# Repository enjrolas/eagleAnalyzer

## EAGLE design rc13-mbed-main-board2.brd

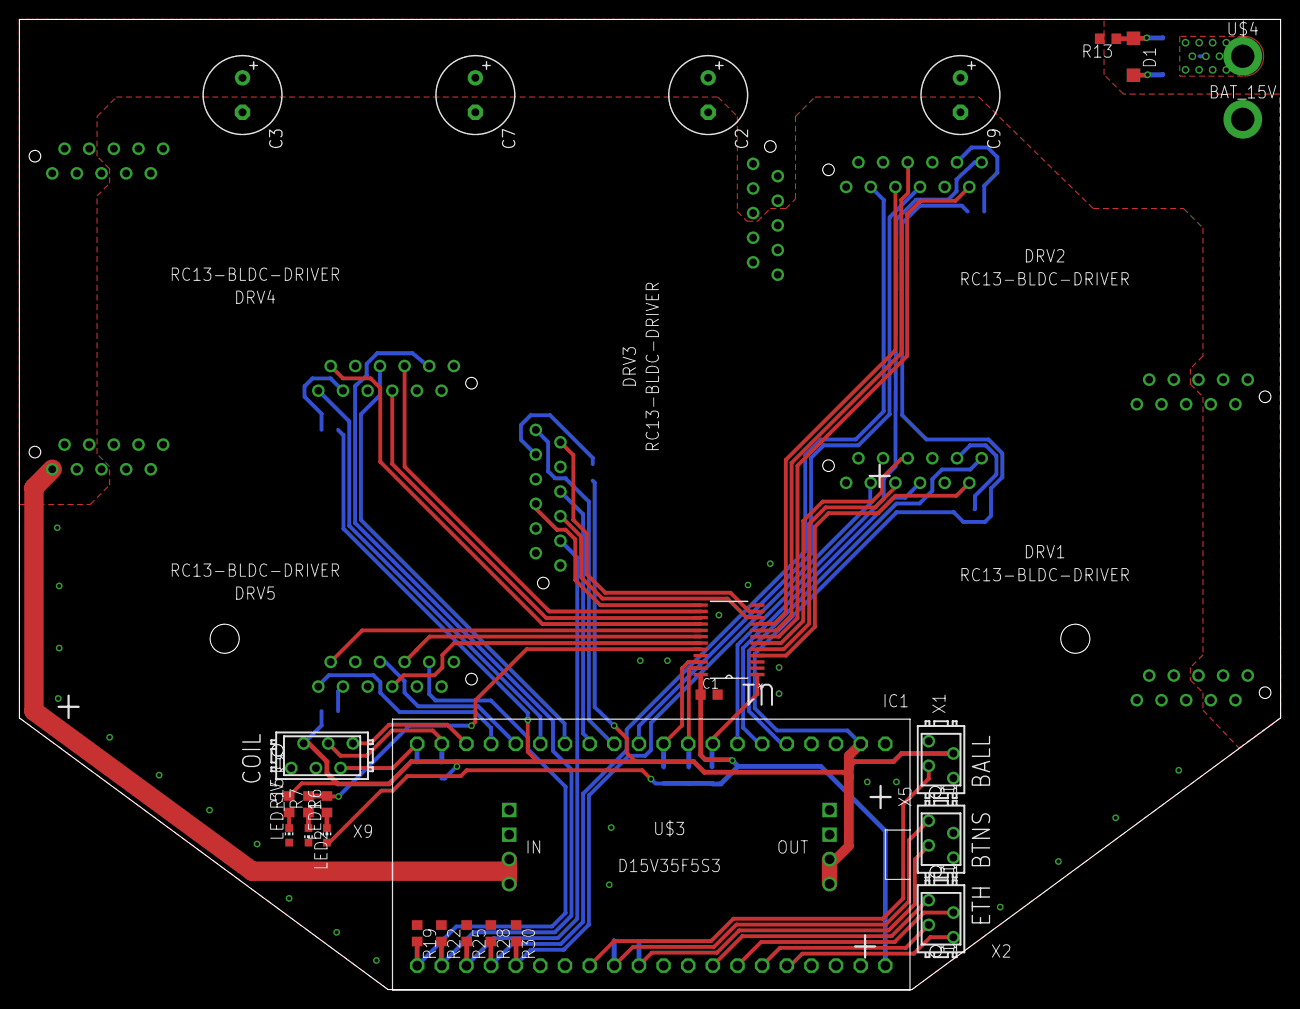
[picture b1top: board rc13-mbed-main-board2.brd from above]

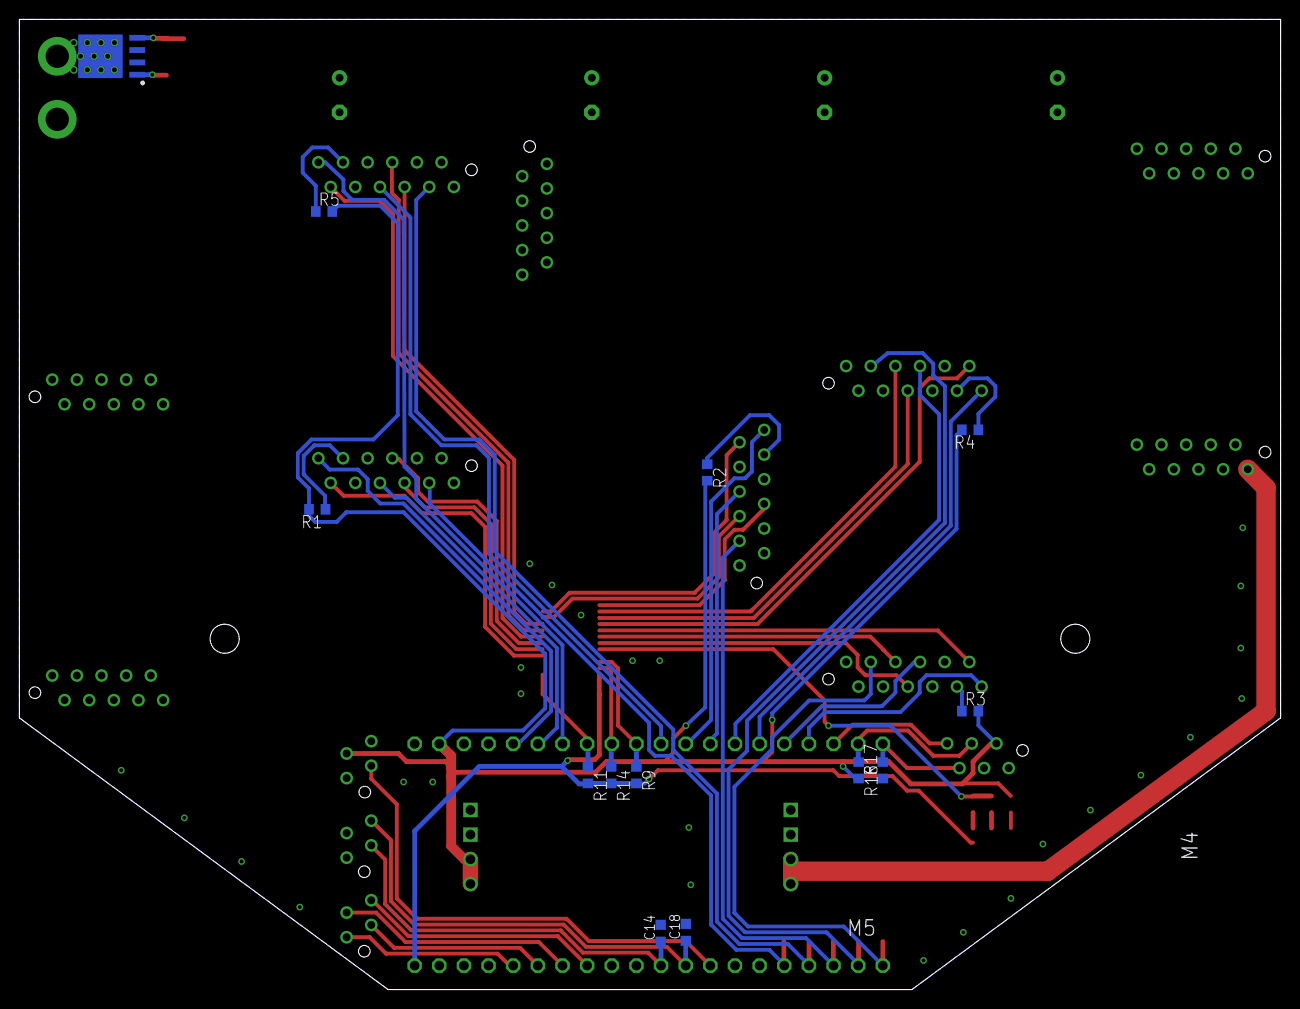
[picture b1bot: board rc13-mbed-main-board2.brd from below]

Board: 2 copper layers, 130.0 x 100.0 mm, 45 parts (13 on the bottom side), 58 nets.

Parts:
BAT_15V: M01_PWR; PWR_HOLE
C1, C14, C18: 100nF; C0603K
C2, C3, C7, C9: 470uF; E3,5-8
D1: 12V; SOD123
DRV1, DRV2, DRV3, DRV4, DRV5: RC13-BLDC-DRIVER
IC1: MBED_MICROCONTROLLER; DIL40_0.9
LED1, LED2: CHIP-LED0603
LED_5V: CHIP-LED0603
R1, R2, R3, R4, R5, R16, R17, R19, R22, R25, R28, R30: 10k; R0603
R6, R7, R9, R11, R14, R15: 2K2; R0603
R13: 100k; R0603
U1: PCA9555PW,118; SOP65P640X110-24N
U$2: MOSFET-N; TO127P600X120-5N
U$3: D15V35F5S3
U$4: M01_PWR; PWR_HOLE
X1: BALL_SENS; MICROMATCH-4
X2: ETH; MICROMATCH-4
X5: BTNS; MICROMATCH-4
X9: COIL; MICROMATCH-6

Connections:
+3V3: C1.1, IC1.40, LED1.A, R9.2, R11.2, R14.2, U1.24
+5V: IC1.2, R1.2, R2.2, R3.2, R4.2, R5.2, R15.2, R16.2, U$3.P$7, U$3.P$8, X1.3, X9.2
+15V: BAT_15V.P$1, C2.+, C3.+, C7.+, C9.+, DRV1.PWR1, DRV1.PWR2, DRV1.PWR3, DRV1.PWR4, DRV1.PWR5, DRV2.PWR1, DRV2.PWR2, DRV2.PWR3, DRV2.PWR4, DRV2.PWR5, DRV3.PWR1, DRV3.PWR2, DRV3.PWR3, DRV3.PWR4, DRV3.PWR5, DRV4.PWR1, DRV4.PWR2, DRV4.PWR3, DRV4.PWR4, DRV4.PWR5, DRV5.PWR1, DRV5.PWR2, DRV5.PWR3, DRV5.PWR4, DRV5.PWR5, R13.2, U$3.EN, U$3.P$5
BALL: IC1.28, X1.2
BAT_GND: U$2.5, U$4.P$1
BRAKE1: DRV1.LOGIC6, U1.6
BRAKE2: DRV2.LOGIC6, U1.8
BRAKE3: DRV3.LOGIC6, U1.13
BRAKE4: DRV4.LOGIC6, U1.15
BRAKE5: DRV5.LOGIC6, U1.19
BTN1: C14.1, IC1.30, X5.2
BTN2: C18.1, IC1.29, X5.4
CHARGE: IC1.20, R17.2, X9.5
COAST1: DRV1.LOGIC11, U1.4
COAST2: DRV2.LOGIC11, U1.7
COAST3: DRV3.LOGIC11, U1.11
COAST4: DRV4.LOGIC11, U1.16
COAST5: DRV5.LOGIC11, U1.17
DIR1: DRV1.LOGIC5, U1.5
DIR2: DRV2.LOGIC5, U1.9
DIR3: DRV3.LOGIC5, U1.10
DIR4: DRV4.LOGIC5, U1.14
DIR5: DRV5.LOGIC5, U1.18
DIRO1: DRV1.LOGIC12, IC1.5
DIRO2: DRV2.LOGIC12, IC1.7
DIRO3: DRV3.LOGIC12, IC1.12
DIRO4: DRV4.LOGIC12, IC1.15
DIRO5: DRV5.LOGIC12, IC1.17
DONE: IC1.18, X9.6
GND: C1.2, C2.-, C3.-, C7.-, C9.-, C14.2, C18.2, D1.A, DRV1.LOGIC1, DRV1.LOGIC2, DRV1.PWR6, DRV1.PWR7, DRV1.PWR8, DRV1.PWR9, DRV1.PWR10, DRV2.LOGIC1, DRV2.LOGIC2, DRV2.PWR6, DRV2.PWR7, DRV2.PWR8, DRV2.PWR9, DRV2.PWR10, DRV3.LOGIC1, DRV3.LOGIC2, DRV3.PWR6, DRV3.PWR7, DRV3.PWR8, DRV3.PWR9, DRV3.PWR10, DRV4.LOGIC1, DRV4.LOGIC2, DRV4.PWR6, DRV4.PWR7, DRV4.PWR8, DRV4.PWR9, DRV4.PWR10, DRV5.LOGIC1, DRV5.LOGIC2, DRV5.PWR6, DRV5.PWR7, DRV5.PWR8, DRV5.PWR9, DRV5.PWR10, IC1.1, LED2.C, LED_5V.A, R17.1, R19.1, R22.1, R25.1, R28.1, R30.1, U1.2, U1.3, U1.12, U1.21, U$2.1, U$2.2, U$2.3, U$3.P$1, U$3.P$2, U$3.P$3, U$3.P$4, X1.1, X5.1, X5.3, X9.1
INT: IC1.8, R11.1, U1.1
KICK: IC1.19, R16.1, X9.4
LED1: R6.2, R7.2, U1.20
unnamed: DRV1.LOGIC10, R1.1
unnamed: DRV2.LOGIC10, R5.1
unnamed: DRV4.LOGIC10, R4.1
unnamed: DRV5.LOGIC10, R3.1
unnamed: DRV3.LOGIC10, R2.1
unnamed: LED1.C, R6.1
unnamed: LED2.A, R7.1
unnamed: LED_5V.C, R15.1
unnamed: D1.C, R13.1, U$2.4
PWM1: DRV1.LOGIC3, IC1.25, R30.2
PWM2: DRV2.LOGIC3, IC1.24, R28.2
PWM3: DRV3.LOGIC3, IC1.23, R25.2
PWM4: DRV4.LOGIC3, IC1.22, R22.2
PWM5: DRV5.LOGIC3, IC1.21, R19.2
RD+: IC1.35, X2.2
RD-: IC1.36, X2.1
SCL: IC1.10, R9.1, U1.22
SDA: IC1.9, R14.1, U1.23
TACHO1: DRV1.LOGIC7, IC1.6
TACHO2: DRV2.LOGIC7, IC1.11
TACHO3: DRV3.LOGIC7, IC1.13
TACHO4: DRV4.LOGIC7, IC1.14
TACHO5: DRV5.LOGIC7, IC1.16
TD+: IC1.33, X2.4
TD-: IC1.34, X2.3

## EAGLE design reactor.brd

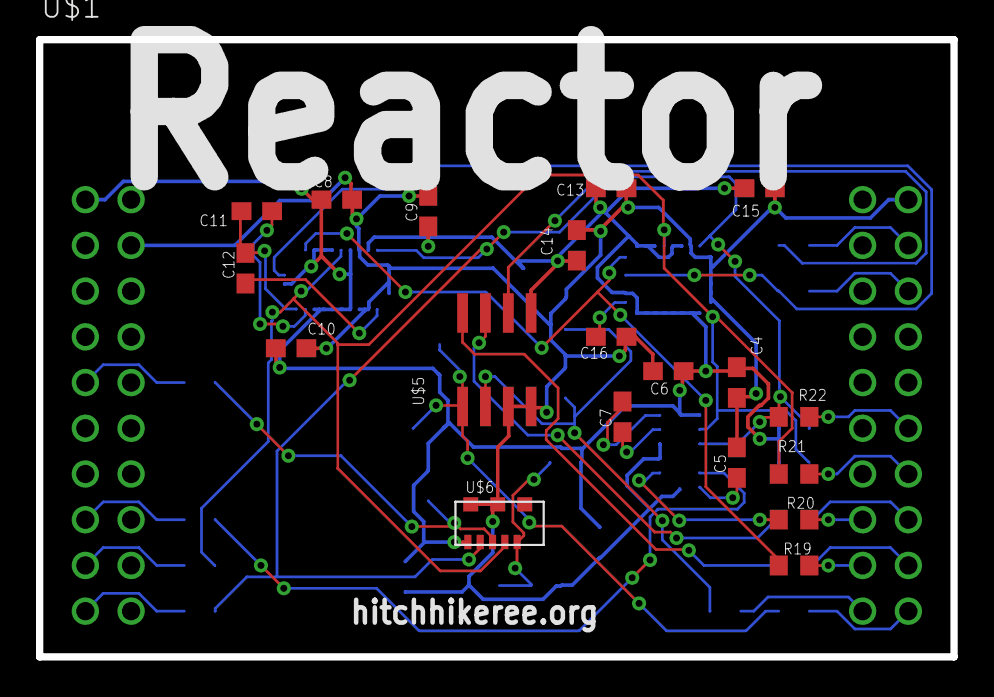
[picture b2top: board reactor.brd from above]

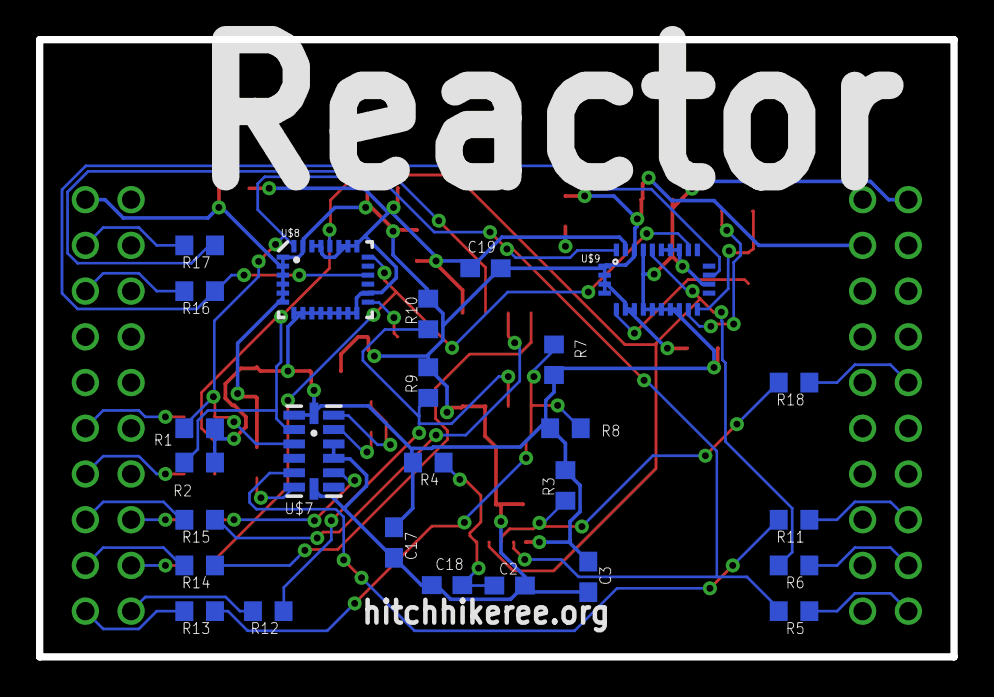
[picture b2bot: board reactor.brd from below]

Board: 2 copper layers, 50.8 x 34.3 mm, 46 parts (26 on the bottom side), 36 nets.

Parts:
C2, C3, C6, C9, C10, C14, C15, C17, C19: 0.1u; C0603
C4, C8, C13, C18: 10u; C0603
C5, C12: 4.7u; C0603
C7, C11: 0.22u; C0603
C16: 10n; C0603
R1, R2: 5.6K, 5%; R0603
R3, R7, R8: 10K; R0603
R4, R5, R6, R11, R12, R13, R14, R15, R16, R17, R18, R19, R20, R21, R22: 33; R0603
R9, R10: 10K, DNI; R0603
U$1: LAUNCHPAD_BOOSTER_PACK
U$5: SOIC8
U$6: VCNL3020
U$7: LGA14
U$8: LGA28-4X5
U$9: LGA28

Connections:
+3V3: C3.1, C4.1, C6.1, C8.1, C9.1, C10.1, C13.1, C14.1, C15.1, C17.1, C19.1, R1.2, R2.1, R3.2, R4.2, R7.1, R8.1, U$1.VCC, U$5.5, U$6.ANODE_E, U$7.1, U$7.14, U$8.7, U$8.8, U$8.9, U$8.10, U$8.11, U$8.12, U$8.13, U$8.14, U$8.16, U$8.21, U$8.22, U$8.23, U$8.25, U$8.26, U$9.8, U$9.9, U$9.10, U$9.11, U$9.12, U$9.16, U$9.21, U$9.22, U$9.23, U$9.25, U$9.27
DRDY: R20.1, U$7.9
GND: C2.2, C3.2, C4.2, C5.2, C6.2, C8.2, C9.2, C10.2, C13.2, C14.2, C15.2, C16.2, C17.2, C18.2, C19.2, R9.2, R10.2, U$1.GND@1, U$1.GND@2, U$5.3, U$5.4, U$6.CATHODE_E, U$6.VSS, U$7.7, U$7.10, U$7.11, U$8.1, U$8.2, U$8.3, U$8.4, U$8.5, U$8.6, U$8.27, U$9.1, U$9.2, U$9.3, U$9.4, U$9.6, U$9.7, U$9.26
I2C_SCL: R2.2, R6.2, R21.1, U$6.SCL, U$7.2, U$8.24, U$9.24
I2C_SDA: R1.1, R5.2, R22.1, U$6.SDA, U$7.3, U$8.28, U$9.28
INT1: R11.2, U$7.5
INT1_A/M: R19.1, U$8.20, U$9.20
INT1_G: R16.1, U$8.18, U$9.17
INT_IR: R3.1, R18.2, U$6.INT
unnamed: C2.1, C18.1, R4.1, U$6.VDD
unnamed: R18.1, U$1.GPIO_INT@1
unnamed: R11.1, U$1.GPIO@1
unnamed: R19.2, U$1.TIM@9
unnamed: R20.2, U$1.TIM@8
unnamed: R6.1, U$1.GPIO@2
unnamed: R5.1, U$1.GPIO@3
unnamed: R21.2, U$1.SPIB_SOMI/I2C_SCL
unnamed: R22.2, U$1.SPIB_SIMO/I2C_SDA
unnamed: R12.2, U$1.TIM@10
unnamed: R15.2, U$1.GPIO@4
unnamed: R14.2, U$1.GPIO@5
unnamed: R13.2, U$1.GPIO@6
unnamed: R17.2, U$1.TIM_OUT
unnamed: R16.2, U$1.GPIO_INT@2
unnamed: C7.1, U$7.12
unnamed: C7.2, U$7.13
unnamed: C5.1, U$7.6
unnamed: C16.1, U$8.15
unnamed: C11.1, U$9.13
unnamed: C11.2, C12.2, U$9.14
unnamed: C12.1, U$9.5
RGB_OUT: R17.1, U$5.6
RGB_S0: R7.2, R8.2, R13.1, U$5.1
RGB_S1: R9.1, R10.1, R12.1, U$5.2
RGB_S2: R15.1, U$5.7
RGB_S3: R14.1, U$5.8

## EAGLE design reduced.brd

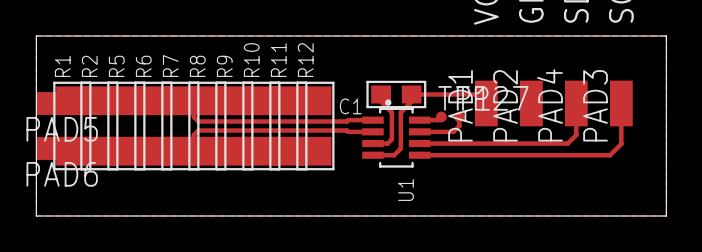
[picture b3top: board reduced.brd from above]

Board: 2 copper layers, 35.0 x 10.0 mm, 20 parts (0 on the bottom side), 8 nets.

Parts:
C1: 0.1µF; 0603
PAD1, PAD2, PAD3, PAD4, PAD5, PAD6: SMD1,27-2,54
R1, R2, R5, R6, R7, R8, R9, R10, R11, R12: 1R; 1206
TP1, TP27: TPTP06R; TP06R
U1: INA219BIDCNT; SOT23-8

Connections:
GND: C1.2, PAD2.1, U1.3
unnamed: TP27.TP, U1.7
unnamed: TP1.TP, U1.8
SCL: PAD3.1, U1.5
SDA: PAD4.1, U1.6
VCC: C1.1, PAD1.1, U1.4
VIN+: PAD5.1, R1.2, R2.2, R5.2, R6.2, R7.2, R8.2, R9.2, R10.2, R11.2, R12.2, U1.1
VIN-: PAD6.1, R1.1, R2.1, R5.1, R6.1, R7.1, R8.1, R9.1, R10.1, R11.1, R12.1, U1.2

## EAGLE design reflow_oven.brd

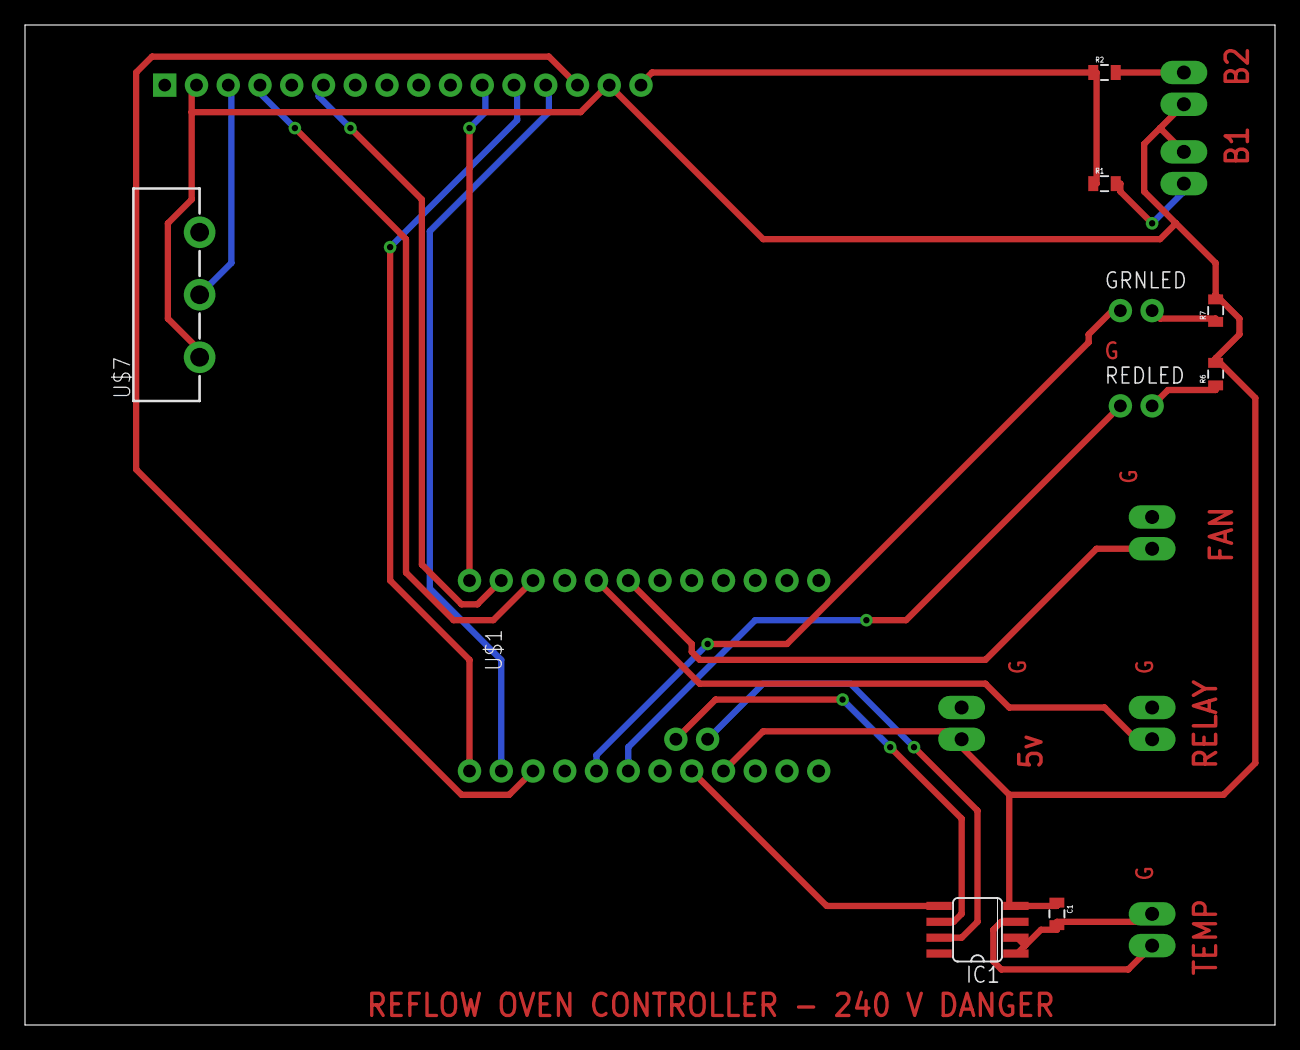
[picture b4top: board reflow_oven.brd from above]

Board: 2 copper layers, 100.0 x 80.0 mm, 17 parts (0 on the bottom side), 21 nets.

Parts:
C1: 100nF; 0805
FAN: 1X02_LONGPADS
GRNLED: 1X02_NO_SILK
IC1: MAX6675; SO08
POWER: 1X02_LONGPADS
R1, R2: 2.2K; 0805
R6, R7: 470R; 0805
REDLED: 1X02_NO_SILK
RELAY: 1X02_LONGPADS
SWITCH1, SWITCH2: 1X02_LONGPADS
THERMO: 1X02_LONGPADS
U1: LCD-16X2NOHOLES; LCD-16X2_NOHOLES
U$1: ARDUINO_MINI
U$7: POT_ALPHA_RV16AF-20

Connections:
5V: C1.1, IC1.4, POWER.1, R6.2, R7.2, SWITCH1.1, SWITCH2.1, U1.2, U1.15, U$1.21, U$7.1
A0: GRNLED.1, U$1.17
A1: REDLED.1, U$1.18
A3: IC1.5, U$1.20
A4: IC1.6, U$1.27
A5: IC1.7, U$1.26
D4: FAN.1, U$1.7
D5: RELAY.1, U$1.8
D7: U1.4, U$1.10
D8: U1.6, U$1.11
D9: U1.11, U$1.12
D10: U1.12, U$1.13
D11: U1.13, U$1.14
D12: U1.14, U$1.15
GND: C1.2, FAN.2, IC1.1, IC1.2, POWER.2, R1.1, R2.1, RELAY.2, THERMO.2, U1.1, U1.5, U1.16, U$1.4, U$1.23, U$7.3
unnamed: U1.3, U$7.2
unnamed: R1.2, SWITCH2.2
unnamed: IC1.3, THERMO.1
unnamed: R6.1, REDLED.2
unnamed: GRNLED.2, R7.1
unnamed: R2.2, SWITCH1.2

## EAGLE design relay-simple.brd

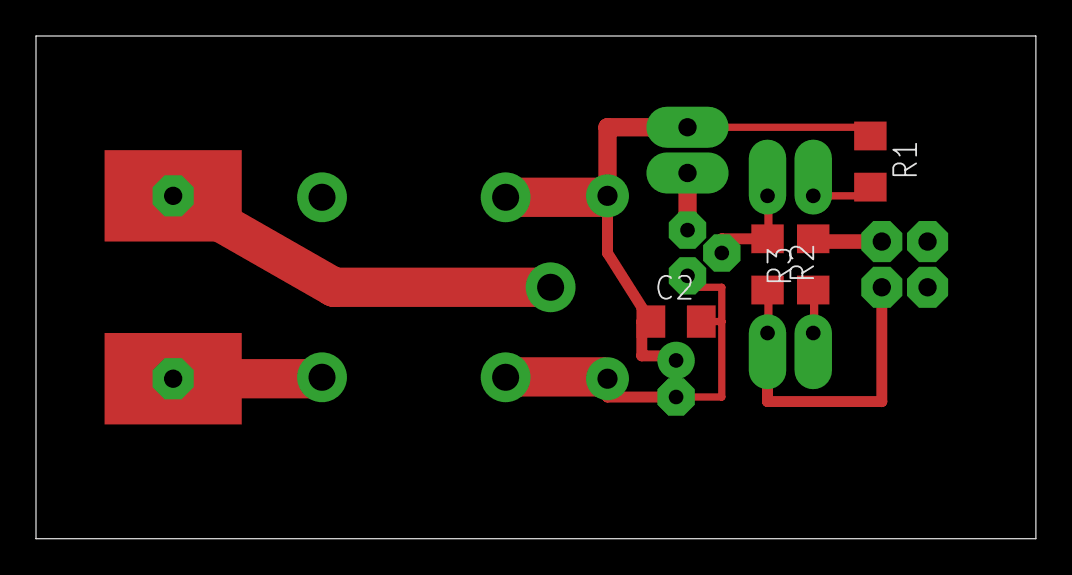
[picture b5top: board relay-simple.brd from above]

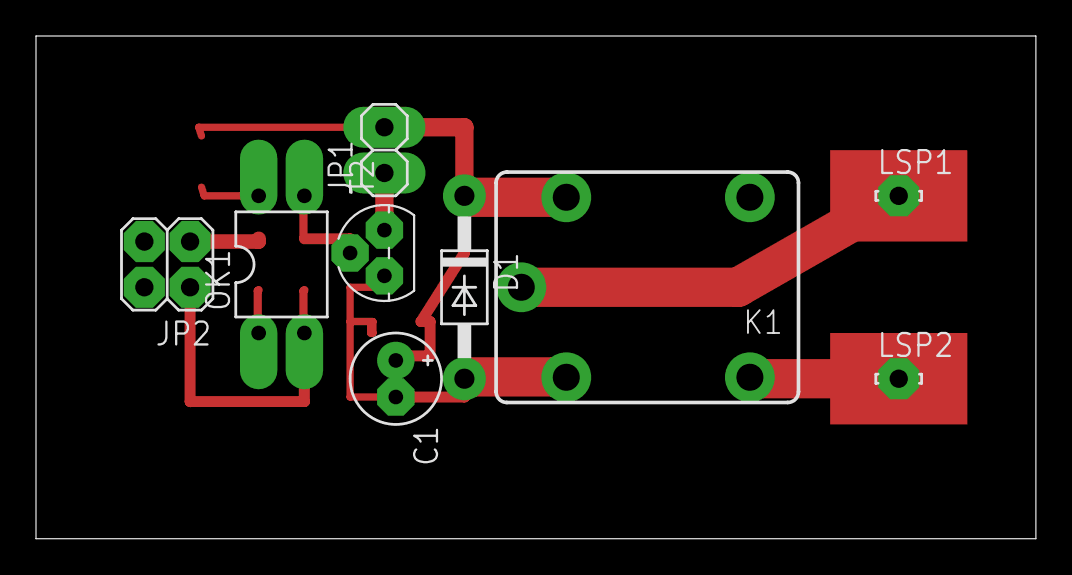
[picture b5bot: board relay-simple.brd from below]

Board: 2 copper layers, 55.5 x 27.9 mm, 13 parts (9 on the bottom side), 9 nets.

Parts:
C1: E2-5
C2: C1206
D1: 1N4004; DO41-10
JP1: 1X02
JP2: 2X02
K1: CQ1-12V; CQ1
LSP1, LSP2: LSP10
OK1: PC817; DIL04
R1, R2, R3: R1206
T2: TO92

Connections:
+12V: C1.+, C2.1, D1.C, JP1.2, K1.1, R1.1
GND: JP1.1, JP2.2, OK1.2, R2.2, T2.1
unnamed: OK1.3, R2.1, T2.2
unnamed: C1.-, C2.2, D1.A, K1.2, T2.3
unnamed: OK1.4, R1.2
unnamed: OK1.1, R3.1
unnamed: JP2.1, R3.2
unnamed: K1.C, LSP1.MP
unnamed: K1.NO, LSP2.MP

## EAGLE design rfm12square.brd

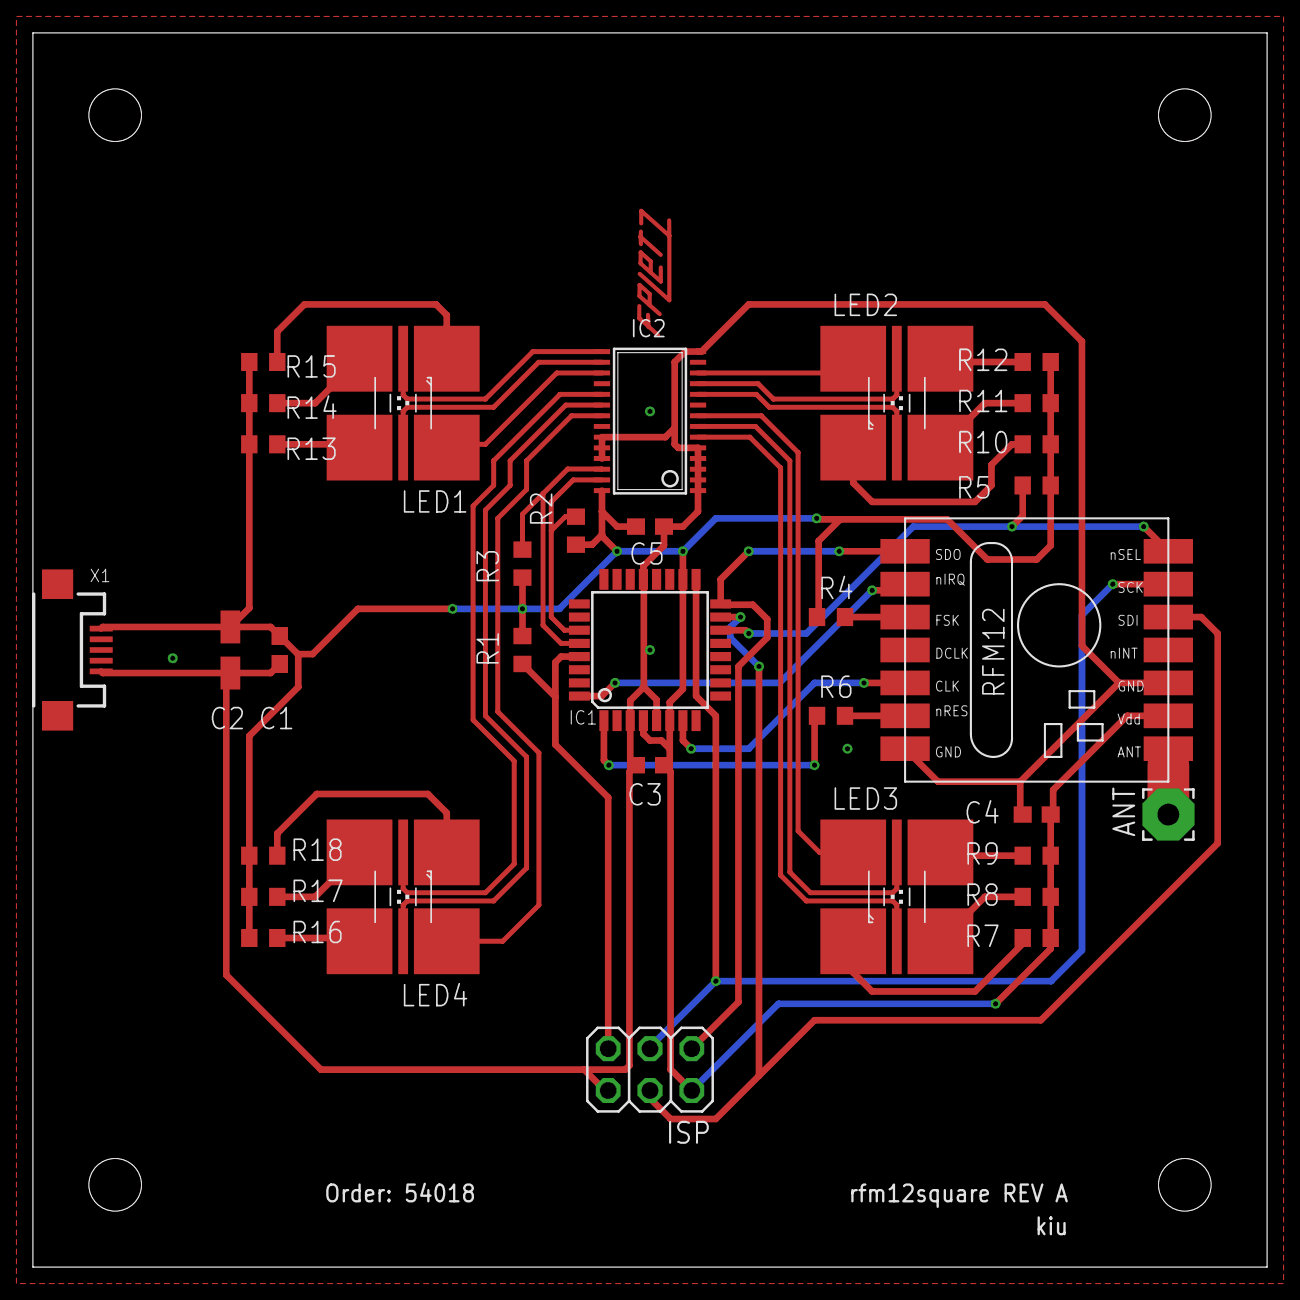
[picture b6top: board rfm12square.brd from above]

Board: 2 copper layers, 75.0 x 75.0 mm, 33 parts (0 on the bottom side), 39 nets.

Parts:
ANT: WIREPAD3,17/1,3; 3,17/1,3
C1, C3, C4, C5: 100nF; C0603
C2: 10uF; CT3216
IC1: MEGA8-AI; TQFP32-08
IC2: PCA9635PW; TSSOP28
ISP: 2X03
LED1, LED2, LED3, LED4: MULTILED_LRTB_G6TG; P-LCC-6_TOPLED
R1, R4, R6: 10k; R0603
R2, R3: 4k7; R0603
R5: 100k; R0603
R7, R10, R15, R18: 145; R0603
R8, R9, R11, R12, R13, R14, R16, R17: 90; R0603
U$1: FRM12; RFM12
X1: USB-MICROB

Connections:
CLK: IC1.7, U$1.5
GND: C1.2, C2.-, C3.2, C4.2, C5.1, IC1.3, IC1.5, IC1.21, IC2.1, IC2.2, IC2.3, IC2.4, IC2.5, IC2.14, IC2.23, IC2.24, IC2.25, ISP.6, U$1.7, U$1.10, X1.GND
MISO: IC1.16, ISP.1, U$1.1
MOSI: IC1.15, ISP.4, U$1.12
unnamed: LED4.A2, R17.1
unnamed: LED1.A2, R14.1
unnamed: LED4.A3, R16.1
unnamed: LED4.A1, R18.1
unnamed: LED1.A3, R13.1
unnamed: IC2.6, LED3.C2
unnamed: IC2.7, LED3.C3
unnamed: IC2.8, LED3.C1
unnamed: IC2.10, LED2.C2
unnamed: IC2.11, LED2.C3
unnamed: IC2.12, LED2.C1
unnamed: IC2.15, LED1.C2
unnamed: R4.1, U$1.3
unnamed: R6.2, U$1.6
unnamed: LED1.A1, R15.1
unnamed: ANT.1, U$1.8
unnamed: IC2.16, LED1.C3
unnamed: IC2.17, LED1.C1
unnamed: LED2.A3, R12.1
unnamed: IC2.19, LED4.C2
unnamed: IC2.20, LED4.C3
unnamed: IC2.21, LED4.C1
unnamed: LED2.A2, R11.1
unnamed: LED2.A1, R10.1
unnamed: LED3.A1, R7.1
unnamed: LED3.A3, R9.1
unnamed: LED3.A2, R8.1
RFIRQ: IC1.32, U$1.2
RFRST: IC1.1, R6.1
RST: IC1.29, ISP.5, R1.1
SCK: IC1.17, ISP.3, U$1.13
SCL: IC1.28, IC2.26, R3.1
SDA: IC1.27, IC2.27, R2.1
SS: IC1.14, R5.2, U$1.14
VCC: C1.1, C2.+, C3.1, C4.1, C5.2, IC1.4, IC1.6, IC1.18, IC2.28, ISP.2, R1.2, R2.2, R3.2, R4.2, R5.1, R7.2, R8.2, R9.2, R10.2, R11.2, R12.2, R13.2, R14.2, R15.2, R16.2, R17.2, R18.2, U$1.9, X1.VBUS

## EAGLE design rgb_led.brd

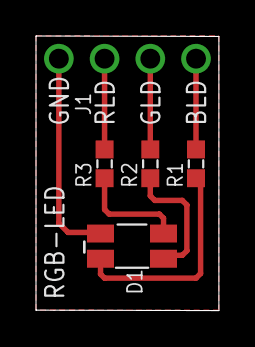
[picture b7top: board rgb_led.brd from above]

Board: 2 copper layers, 10.2 x 15.3 mm, 5 parts (0 on the bottom side), 7 nets.

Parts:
D1: D1210
J1: PHSP254P1016X254X1154-4S
R1, R2, R3: 390; RESC0603

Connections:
+3V3: D1.1, J1.1
unnamed: D1.2, R1.P$2
unnamed: D1.4, R2.P$2
unnamed: D1.3, R3.P$2
unnamed: J1.4, R1.P$1
unnamed: J1.2, R3.P$1
unnamed: J1.3, R2.P$1

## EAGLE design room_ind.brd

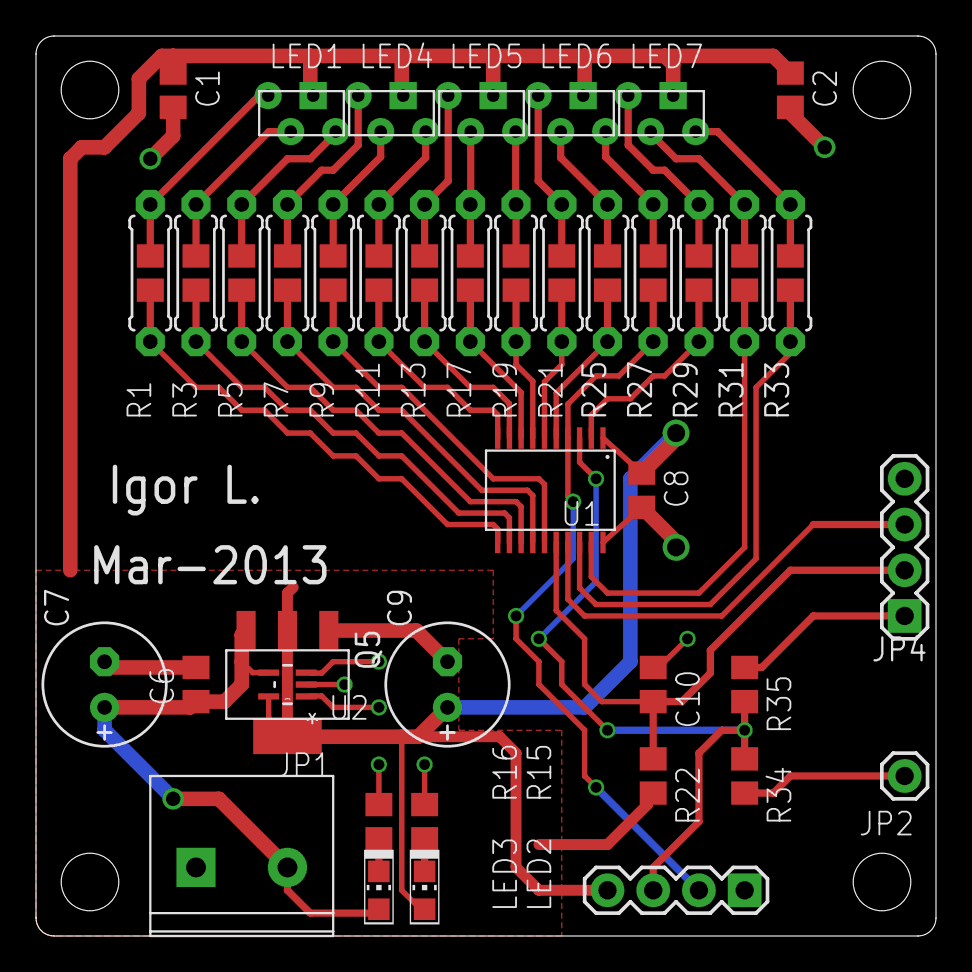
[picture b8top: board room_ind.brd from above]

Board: 2 copper layers, 50.0 x 50.0 mm, 56 parts (0 on the bottom side), 39 nets.

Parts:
C1, C2, C6, C8: 0.47uF; C0805
C7, C9: 100 uF; E2,5-7
C10: 2.2nf; C0805
JP1: +5V; BLUE_TERM
JP2: RXD_5V; 1X01
JP3, JP4: 1X04
LED1, LED4, LED5, LED6, LED7: RGB_5MM
LED2: GREEN; CHIP-LED0805
LED3: RED; CHIP-LED0805
Q5: TLV1117; SOT223-4
R1, R3, R5, R7, R9, R11, R13, R17, R19, R21, R24, R26, R28, R30, R32, R34: 470; R0805
R2, R4, R6, R8, R10, R12, R14, R18, R20, R23, R25, R27, R29, R31, R33: 470; 0207/7
R15, R16, R35: 1K; R0805
R22: 47K; R0805
U1: G2XX3---PW20; PW20
U2: TPS71533_DCK_5; DCK5

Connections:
+3V3: C1.1, C2.1, C8.1, C9.+, JP3.4, LED1.1, LED2.A, LED4.1, LED5.1, LED6.1, LED7.1, Q5.2, Q5.4, R22.2, U1.1, U2.5
+5V: C6.1, C7.+, JP1.2, LED3.A, Q5.3, U2.4
GND: C1.2, C2.2, C6.2, C7.-, C8.2, C9.-, C10.2, JP1.1, JP3.1, JP4.1, Q5.1, R15.1, R16.1, R35.1, U1.20, U2.2
unnamed: LED1.3, R3.2, R4.2
unnamed: LED1.4, R1.2, R2.2
unnamed: LED1.2, R5.2, R6.2
unnamed: JP2.1, R34.2
unnamed: LED2.C, R15.2
unnamed: LED3.C, R16.2
unnamed: LED4.3, R9.2, R10.2
unnamed: LED4.4, R7.2, R8.2
unnamed: LED4.2, R11.2, R12.2
unnamed: LED5.3, R17.2, R18.2
unnamed: LED5.4, R13.2, R14.2
unnamed: LED5.2, R19.2, R20.2
unnamed: LED6.3, R24.2, R25.2
unnamed: LED6.4, R21.2, R23.2
unnamed: LED6.2, R26.2, R27.2
unnamed: LED7.3, R30.2, R31.2
unnamed: LED7.4, R28.2, R29.2
unnamed: LED7.2, R32.2, R33.2
RST: C10.1, JP4.2, R22.1, U1.16
RXD: JP3.3, R34.1, R35.2, U1.3
T1B: R3.1, R4.1, U1.12
T1G: R1.1, R2.1, U1.11
T1R: R5.1, R6.1, U1.13
T2B: R9.1, R10.1, U1.15
T2G: R7.1, R8.1, U1.14
T2R: R11.1, R12.1, U1.10
T3B: R17.1, R18.1, U1.8
T3G: R13.1, R14.1, U1.9
T3R: R19.1, R20.1, U1.7
T4B: R24.1, R25.1, U1.5
T4G: R21.1, R23.1, U1.6
T4R: JP3.2, R26.1, R27.1, U1.4
T5B: R30.1, R31.1, U1.19
T5G: R28.1, R29.1, U1.2
T5R: R32.1, R33.1, U1.18
TEST: JP4.3, U1.17

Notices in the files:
parts and their libraries:
nxp_sot669: Licensing: CC v3.0 Share-Alike You are welcome to use this library for commercial purposes.
